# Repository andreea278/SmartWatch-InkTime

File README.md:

# SmartWatch InkTime 

Proiect de dezvoltare a unui ceas inteligent bazat pe microcontrolerul Nordic nRF52840, echipat cu un afișaj E-Ink și senzori pentru monitorizarea activității.

---

## Diagramă Bloc

---
Acest proiect reprezintă o platformă open-hardware de tip smartwatch, proiectată pentru flexibilitate maximă și eficiență energetică ridicată. Construit în jurul microcontrolerului nRF52840 , dispozitivul oferă control total la nivel de regiștri pentru proiecte embedded avansate.

- **[nRF52840](https://www.nordicsemi.com/Products/nRF52840)(Microcontroler):** System on Chip bazat pe ARM Cortex-M4F tactat la 64 MHz. Include suport nativ pentru Bluetooth 5 / BLE și radio 2.4 GHz. Dispune de 1 MB Flash și 256 KB RAM și oferă interfețe versatile: SPI, I2C, UART și GPIO pentru comunicarea cu celelalte module.
- **[E-Paper 1.54"](https://www.waveshare.com/wiki/1.54inch_e-Paper_Module):** Ecran cu consum redus de energie, rezoluție 200x200 pixeli, comunică cu MCU-ul prin interfața SPI.
- **[BQ25180](https://www.ti.com/product/BQ25180)(Încărcător LiPo):** IC pentru încărcarea bateriei Li-Ion/Li-Po, controlat prin I2C. Gestionează alimentarea de 5V de la portul USB și oferă funcții de *power path management*.
- **[MAX17048](https://www.analog.com/en/products/max17048.html)(Fuel Gauge):** Cip pentru monitorizarea precisă a nivelului bateriei (State-of-Charge).
- **[RT6160](https://www.richtek.com/Products/Switching%20Regulators/Buck-Boost%20Converter/RT6160)(Regulator Buck-Boost):** Reglează tensiunea bateriei pentru a furniza o ieșire stabilă de 3.3V necesară componentelor sistemului.
- **Baterie LiPo (250 mAh):** Sursa principală de energie a dispozitivului.
- **[USBLC6-2](https://www.st.com/en/protections-and-safety/usblc6-2.html) (Protecție USB):** Protecție ESD (Electrostatic Discharge) pentru portul USB-C, prevenind deteriorarea componentelor interne.
- **[BMA423](https://www.bosch-sensortec.com/products/motion-sensors/accelerometers/bma423/):** Senzor MEMS pe 3 axe, ultra-low-power, optimizat pentru wearables, oferind funcții integrate precum numărarea pașilor, recunoașterea activității și detectarea mișcării prin întreruperi.
- **[DRV2605L](https://www.ti.com/product/DRV2605L) (Driver Haptic):** Driver controlat prin I2C pentru motorul de vibrații.
- [FIT0774](https://www.dfrobot.com/product-2264.html): Shaker
-  **[TC2030-IDC](https://www.tag-connect.com/product/tc2030-idc/)**: Conector programare SWD.
- **Cristale de tact:**
  - **[32 MHz (X1)](https://www.digikey.ro/en/products/detail/abracon-llc/ABM8G-32.000MHZ-18-D2Y-T/2269926):** Asigură frecvența principală de operare pentru MCU.
  - **[32.768 kHz (X2)](https://www.digikey.ro/en/products/detail/epson/FC-135-32.7680KA-A3/4522301):** Folosit pentru ceasul de timp real (RTC) și menținerea acurateței temporale.

## Bill of Materials (BOM)

Aceasta este lista principală de componente pentru proiectul smartwatch-ului bazat pe nRF52840.

| Component | Descriere | Cantitate | Producător | Cod Piesă | Datasheet |
| :--- | :--- | :---: | :--- | :--- | :---: |
| **nRF52840** | BLE Microcontroller | 1 | Nordic Semiconductor | nRF52840 | [Link](https://files.seeedstudio.com/wiki/XIAO-BLE/Nano_BLE_MCU-nRF52840_PS_v1.1.pdf) |
| **BMA423** | Accelerometru 3-axe (IMU) | 1 | Bosch | BMA423 | [Link](https://watchy.sqfmi.com/assets/files/BST-BMA423-DS000-1509600-950150f51058597a6234dd3eaafbb1f0.pdf) |
| **BQ25180** | Încărcător baterie / PMIC | 1 | Texas Instruments | BQ25180 | [Link](https://www.ti.com/product/BQ25180) |
| **DRV2605L** | Driver haptic | 1 | Texas Instruments | DRV2605L | [Link](https://www.ti.com/product/BQ25180) |
| **MAX17048** | Fuel gauge | 1 | Analog Devices | MAX17048G+T10 | [Link](https://www.analog.com/en/products/max17048.html) |
| **RT6160** | Buck-boost converter | 1 | Richtek | RT6160AWSC | [Link](https://www.mouser.com/datasheet/2/1458/DS6160A_02-3104604.pdf) |
| **2450AT18B100E** | Antenă chip 2.4GHz | 1 | Johanson Technology | 2450AT18B100E | [Link](https://jlcpcb.com/api/file/downloadByFileSystemAccessId/8588940948130156544) |
| **TC2030-IDC** | Conector programare | 1 | Tag-Connect | TC2030-IDC | [Link](https://www.lcsc.com/datasheet/C5444772.pdf) |
| **USB-C Connector** | Interfață alimentare/date | 1 | Kinghelm | KH-TYPE-C-16P | [Link](https://jlcpcb.com/api/file/downloadByFileSystemAccessId/8588905154556923904) |
| **FPC Connector** | Conector display e-paper | 1 | Molex | 503480-2400 | [Link](https://www.molex.com/content/dam/molex/molexdotcom/products/automated/enus/salesdrawingpdf/503/503480/5034802400_sd.pdf?inline) |
| **Push Buttons** | Switch-uri tactile | 3 | Panasonic | EVP-AKE31A | [Link](https://wmsc.lcsc.com/wmsc/upload/file/pdf/v2/lcsc/2301111010_PANASONIC-EVPAKE31A_C569760.pdf) |
| **MOSFETs** | Comutare putere | 2 | Vishay / Diodes Inc. | SI1308EDL / DMG2305UX | [Link](https://www.lcsc.com/datasheet/C469327.pdf) |
| **Diodes** | Diode Schottky | 3 | ON Semiconductor | MBR0530 | [Link](https://www.lcsc.com/datasheet/C77336.pdf) |
| **ESD Protection** | Protecție USB | 1 | STMicroelectronics | USBLC6-2SC6 | [Link](https://www.lcsc.com/datasheet/C7519.pdf) |
| **Crystal** | 32MHz | 1 | NDK | NX2016SA-32MHZ-EXS00A-CS11336 | [Link](https://wmsc.lcsc.com/wmsc/upload/file/pdf/v2/lcsc/2312080231_NDK-NX2016SA-32MHZ-EXS00A-CS11336_C6134317.pdf) |
| **Crystals** | 32.768kHz | 1 | Seiko Epson | FC-135 32.7680KA-A3 | [Link](https://jlcpcb.com/partdetail/SeikoEpson-FC_135_32_7680KAA3/C2650472) |

---

##  Arhitectură și Specificații Hardware

### 1. Unitatea de Procesare (CPU)
* **Microcontroler:** **nRF52840 (Nordic Semiconductor)**
    * **Arhitectură:** ARM Cortex-M4F (cu FPU), tactat la 64 MHz.
    * **Capabilități:** Suport nativ Bluetooth 5.4 (BLE), radio 2.4 GHz.
    * **Memorie:** 1 MB Flash, 256 KB RAM.
    * **Rol:** Procesare centrală, gestionarea stivei Bluetooth și coordonarea perifericelor.

### 2. Sistemul de Management al Energiei (PMU)
Sistemul utilizează un lanț de alimentare eficient pentru a prelungi durata de viață a bateriei:

* **Încărcare (PMIC):** **BQ25180**
    * Gestionează alimentarea de 5V (USB-C) și oferă protecție integrată.
* **Reglare Tensiune:** **RT6160 (Buck-Boost)**
    * Converteste tensiunea bateriei (3.0V - 4.2V) la o linie stabilă de **3.3V** cu o eficiență de peste 90%.
* **Monitorizare:** **MAX17048 (Fuel Gauge)**
    * Algoritm *ModelGauge* pentru estimarea precisă a nivelului bateriei.
 
 ### 3. Matricea de Comunicare
Sistemul utilizează magistrale digitale pentru a minimiza numărul de pini ocupați:

| Protocol | Componente Conectate | Funcție |
| :--- | :--- | :--- |
| **SPI** | E-Paper Display | Transfer rapid de pixeli pentru refresh. |
| **I2C** | BMA423, BQ25180, DRV2605L, MAX17048 | Magistrală partajată pentru senzori și PMU. |
| **GPIO** | Butoane fizice, Interrupts (BMA423) | Input utilizator și wake-up trigger. |
| **SWD** | Conector TC2030-IDC | Interfață de programare și debugging. |

### 4. Periferice 
* **Afișaj:** E-Paper 1.54" (200x200).
    * *Avantaj:* Consum de energie zero pentru menținerea imaginii (bistabil).
* **Senzor:** **BMA423 (Accelerometru)**.
    * *Rol:* Detecția pașilor, recunoașterea activității și trezirea MCU-ului din `Deep Sleep`.
* **Feedback Haptic:** **DRV2605L** + Motor vibrații.
    * *Rol:* Driver haptic inteligent pentru feedback tactil avansat (click-uri, alerte), controlat via I2C.

---

## 4. Mapare Pini nRF52840

| Pin nRF52840 | Semnal | Componentă | Interfață |
| :--- | :--- | :--- | :--- |
| **P0.00** | XL1 | Cristal X2 (32.768kHz) | XTAL |
| **P0.01** | XL2 | Cristal X2 (32.768kHz) | XTAL |
| **P0.02** | SCK | E-Paper (J1 FPC) | SPI SCK |
| **P0.03** | MOSI | E-Paper (J1 FPC) | SPI MOSI |
| **P0.05** | EPD_CS | E-Paper (J1 FPC) | SPI CS |
| **P0.06** | SDA | BMA423, BQ25180, MAX17048, DRV2605 | I2C SDA |
| **P0.07** | SCL | BMA423, BQ25180, MAX17048, DRV2605 | I2C SCL |
| **P0.08** | IMU_INT1 | BMA423 | GPIO Input |
| **P1.08** | IMU_INT2 | BMA423 | GPIO Input |
| **P0.10** | ALERT | MAX17048 | GPIO Input |
| **P0.11** | PMIC_INT | BQ25180 | GPIO Input |
| **P0.12** | HAPTIC_EN | DRV2605 | GPIO Output |
| **P0.13** | SW_UP | Buton Up | GPIO Input |
| **P0.14** | SW_ENT | Buton Enter | GPIO Input |
| **P0.15** | EPD_DC | E-Paper (J1 FPC) | GPIO |
| **P0.16** | EPD_RST | E-Paper (J1 FPC) | GPIO |
| **P0.17** | EPD_BUSY | E-Paper (J1 FPC) | GPIO Input |
| **P0.18** | RESET | TC2030-IDC | SWD / Reset |
| **P1.02** | SW_DN | Buton Down | GPIO Input |
| **SWDCLK** | SWDCLK | TC2030-IDC | SWD |
| **SWDIO** | SWDIO | TC2030-IDC | SWD |
| **ANT** | RF | Antenă 2450AT18B100E | RF |

---
## 5. Specificații Design PCB

### Reguli de Proiectare 
* **Strat 1 (Top):** Componente și rutare semnal.
* **Strat 2 (Internal):** Plan Putere (VCC/3V3).
* **Strat 3 (Internal):** Plan Masă (GND).
* **Strat 4 (Bottom):** Rutare semnal și componente.

### Constrângeri DRC
* **Trasee Putere:** 0.3 mm (îngustate sub BGA).
* **Trasee Date:** 0.15 mm (min).
* **Unghiuri:** Doar 45° sau rotunjite.
* **Antenă:** Zonă "Keep-out" (fără cupru) pe toate straturile sub antenă.
* **Decuplare:** Condensatoarele de 100nF plasate direct pe pinii de alimentare.

### Erori DRC Acceptate
* **Copper Clearance (Aprobat):** În zona fan-out-ului pentru nRF52840, clearance-ul a fost redus manual sub 0.15mm pentru a permite rutarea corectă a pinilor AQFN cu pitch mic.

---

### Design PCB
| **Top Layer** | **Bottom Layer** | **Silkscreen** |
| :---: | :---: | :---: |
|  |  |  |
| **Inner Layer 2 (GND)** | **Inner Layer 3 (Power - C63)** |
|  |  |

### Design Schematic
---

| Pagina 1 - MCU & Power | Pagina 2 - Display & Senzori |
|:---:|:---:|
|  width="300" |  width="300" |

---

### 3D PCB & Carcasa
| **Top View** | 
| :---: | 
|  | 
**Side View** |
|  |
|  **SmartWatch Components** |
|  |

---

## 6. Structură 
* `Hardware/` - Fișierele sursă `.sch` și `.brd` .
* `Manufacturing/` - Fișiere Gerber, BOM și Pick & Place.
* `Mechanical/` - Modelul 3D al dispozitivului în format `.f3d` și `.step` (exploded view).
* `Images/` - Randări și screenshot-uri ale proiectului.

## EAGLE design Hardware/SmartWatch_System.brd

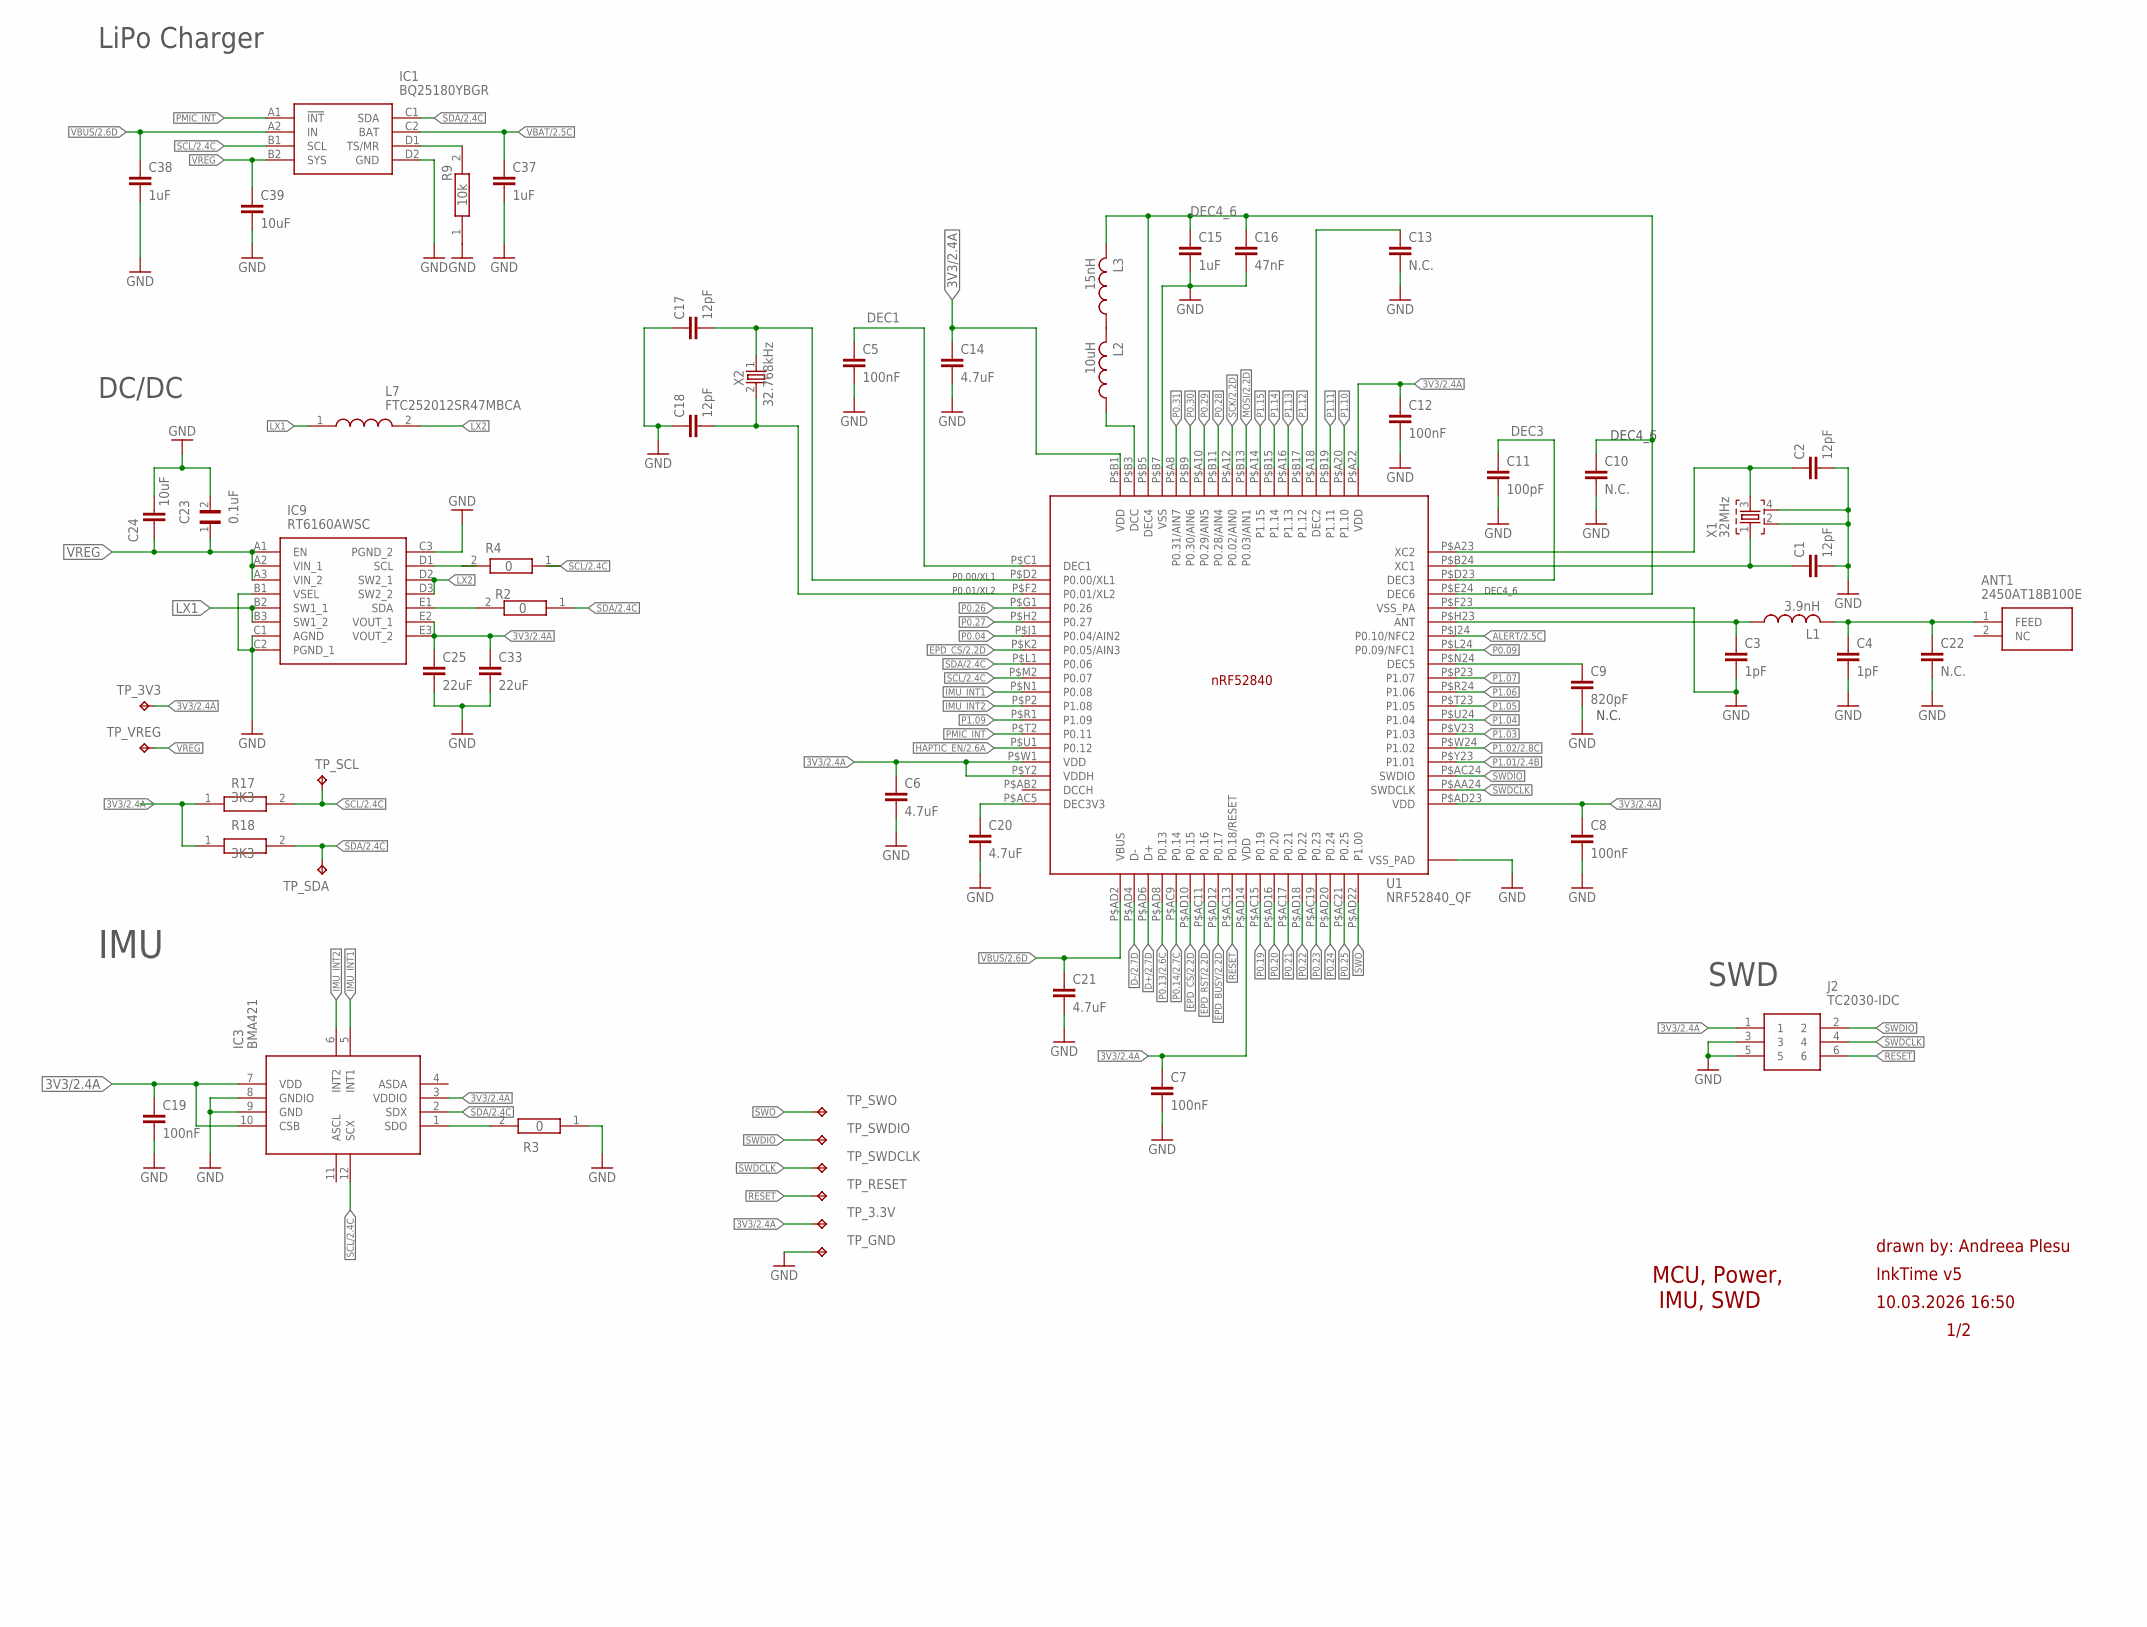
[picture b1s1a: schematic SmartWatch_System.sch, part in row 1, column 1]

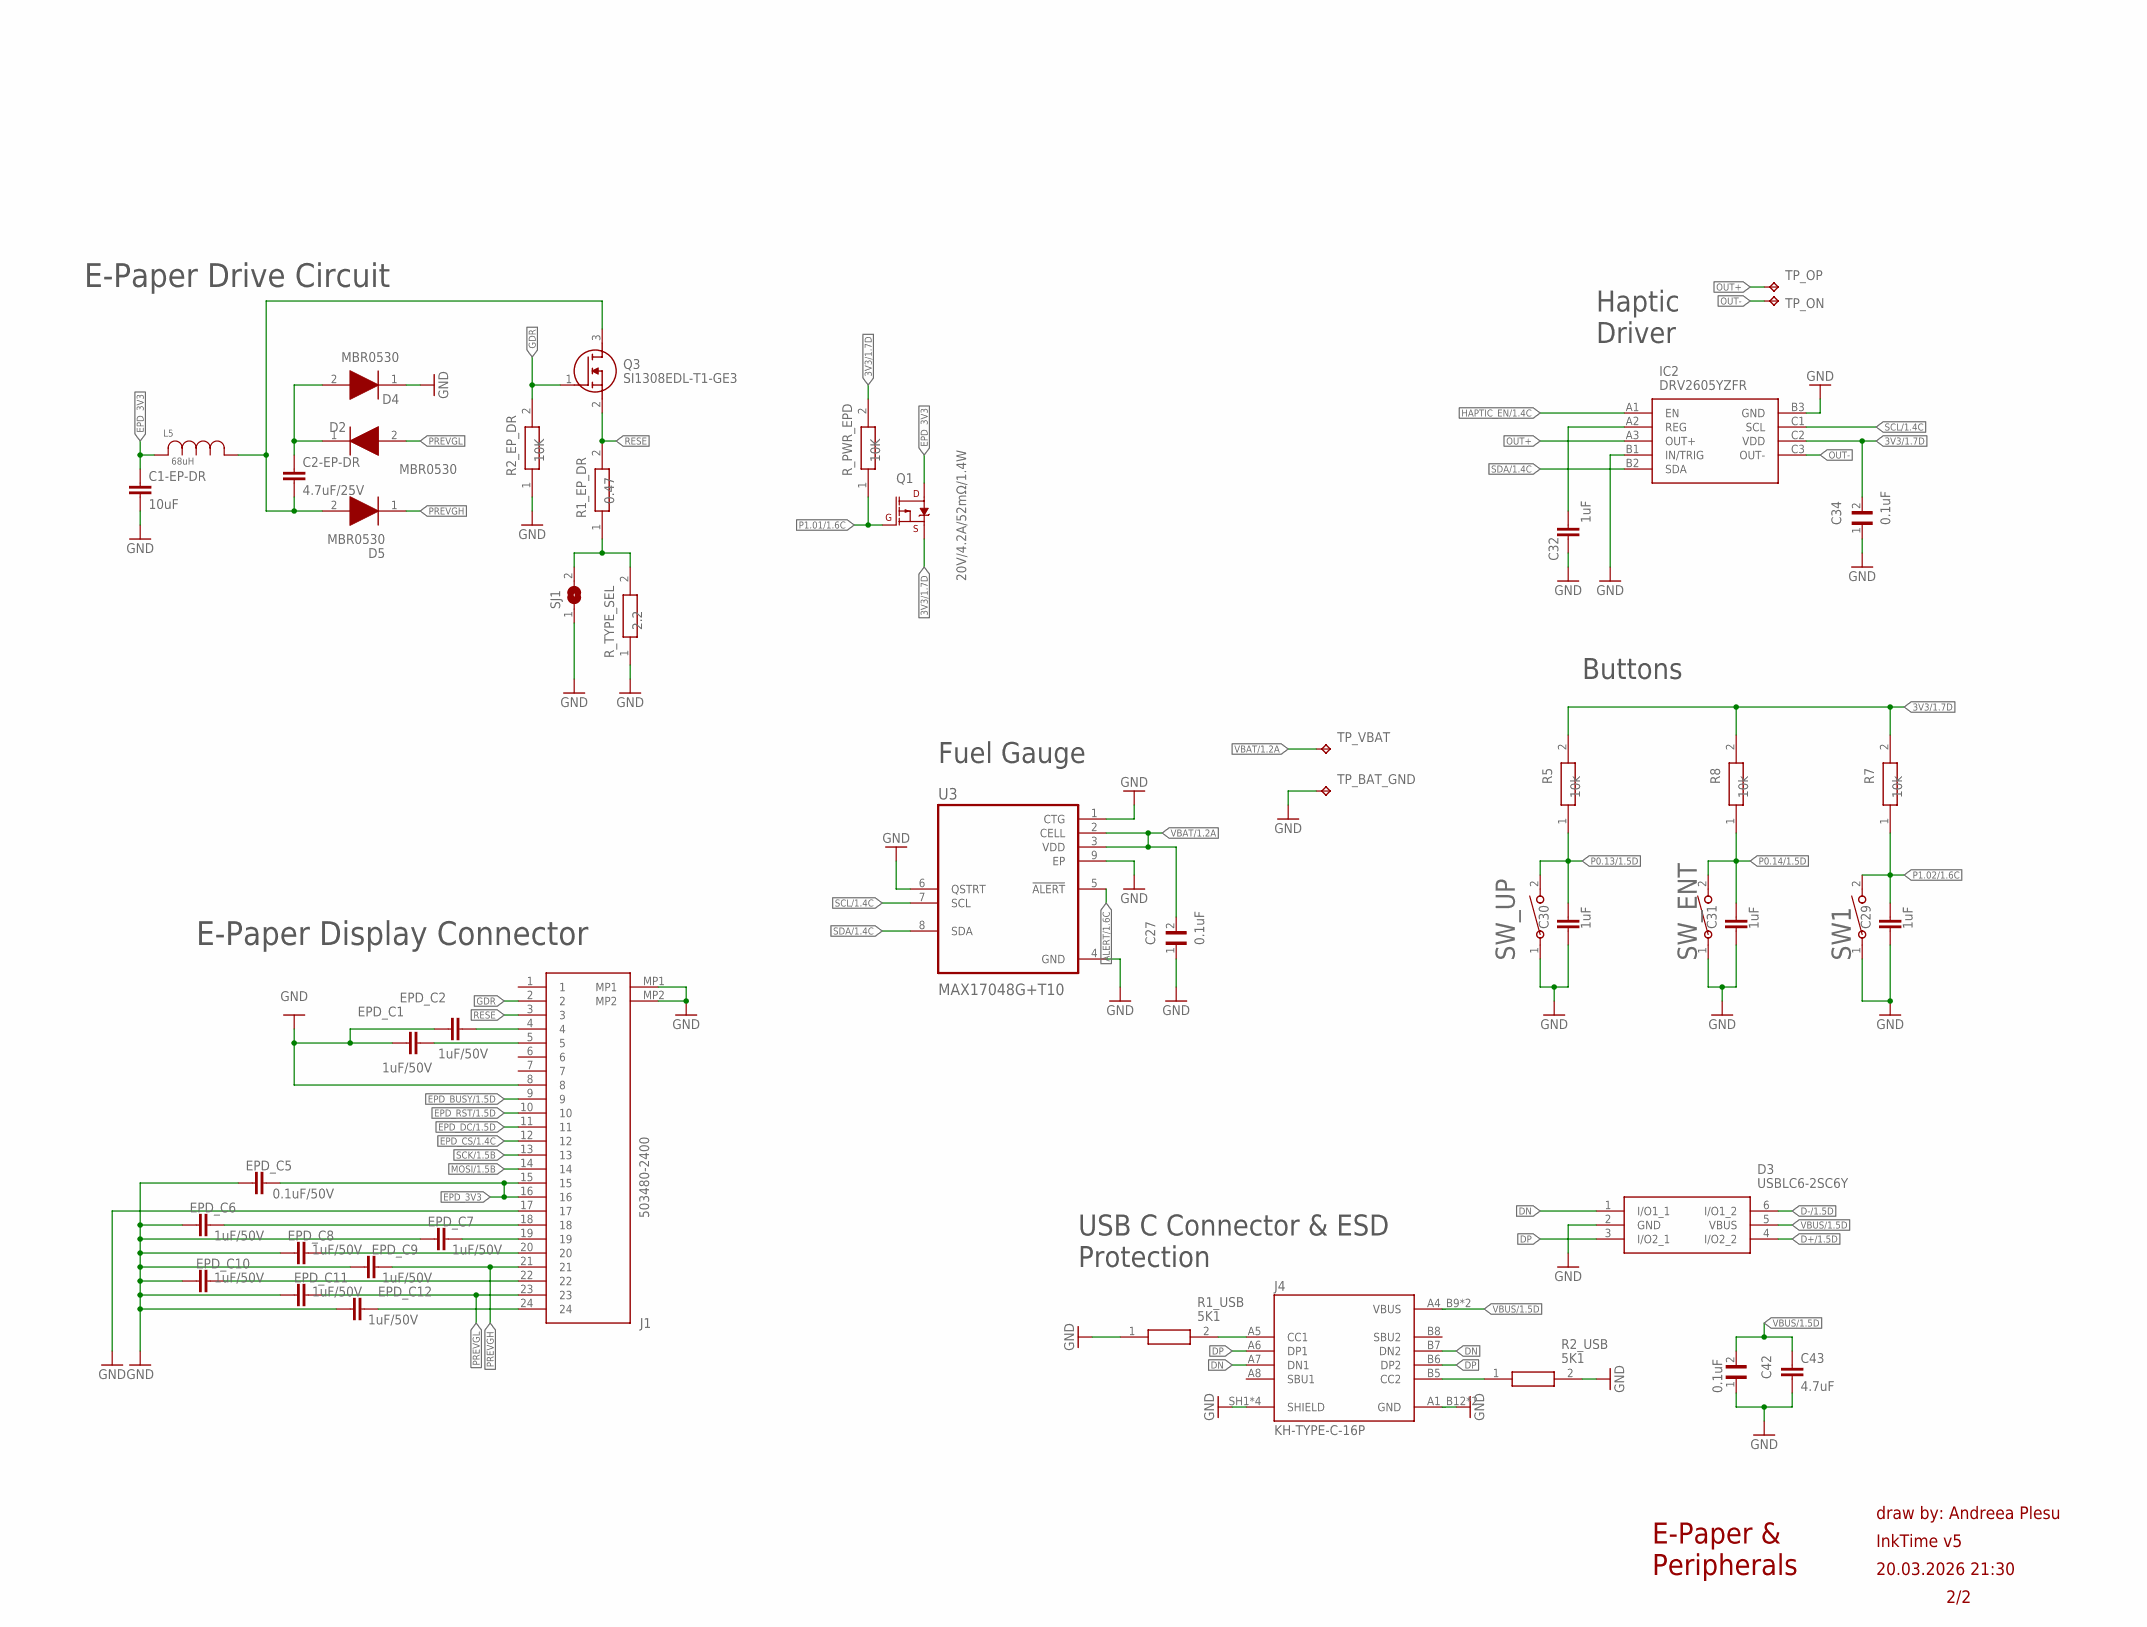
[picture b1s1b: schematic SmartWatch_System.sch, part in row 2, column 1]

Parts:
ANT1: 2450AT18B100E; 2450AT18B100E_ANTC3216X140N
C1, C2, C17, C18: 12pF; NORDIC_NRF_3_RESC0201_L
C1-EP-DR: 10uF; NORDIC_NRF_3_RESC0402_L
C2-EP-DR: 4.7uF/25V; NORDIC_NRF_3_RESC0402_L
C3, C4: 1pF; NORDIC_NRF_3_RESC0201_L
C5, C7, C8, C12, C19: 100nF; NORDIC_NRF_3_RESC0201_L
C6, C20, C21: 4.7uF; NORDIC_NRF_3_RESC0402_L
C9: 820pF; NORDIC_NRF_3_RESC0201_L
C10, C13, C22: N.C.; NORDIC_NRF_3_RESC0201_L
C11: 100pF; NORDIC_NRF_3_RESC0201_L
C14, C43: 4.7uF; PERFECT_0402_0402
C15, C29, C30, C31, C37, C38: 1uF; PERFECT_0402_0402
C16: 47nF; NORDIC_NRF_3_RESC0201_L
C23, C27: 0.1uF; GRM011R60J152KE01L_2_CAPC0201X13N
C24, C39: 10uF; PERFECT_0402_0402
C25, C33: 22uF; NORDIC_NRF_3_RESC0402_L
C32: 1uF; NORDIC_NRF_3_RESC0402_L
C34, C42: 0.1uF; NORDIC_NRF_3_RESC0201_L
D2, D4, D5: MBR0530; ESP32_C6_LIBRARY_5_SOD3716X135N
D3: USBLC6-2SC6Y; ESP32_C6_LIBRARY_3_SOT95P280X145-6N
EPD_C1, EPD_C2, EPD_C6, EPD_C7, EPD_C8, EPD_C9, EPD_C10, EPD_C11, EPD_C12: 1uF/50V; NORDIC_NRF_3_RESC0402_L
EPD_C5: 0.1uF/50V; NORDIC_NRF_3_RESC0201_L
IC1: BQ25180YBGR; BQ25180YBGR_BGA8C40P2X4_100X155X50
IC2: DRV2605YZFR; DRV2605YZFR_BGA9C50P3X3_144X144X62
IC3: BMA421; BMA423_BMA423
IC9: RT6160AWSC; RT6160AWSC_BGA15C40P3X5_140X230X60
J1: 503480-2400; 503480-2400_5034802400
J2: TC2030-IDC; TC2030-IDC_TC2030IDC
J4: KH-TYPE-C-16P; KH-TYPE-C-16P_KINGHELM_KH-TYPE-C-16P
L1: 3.9nH; NORDIC_NRF_2_RESC0402_L
L2: 10uH; NORDIC_NRF_2_RESC0402_L
L3: 15nH; NORDIC_NRF_2_RESC0402_L
L5: 68uH; ESP32_C6_LIBRARY_2_IND_4828-WE-TPC_WRE
L7: FTC252012SR47MBCA; MLP2016SR47MT0S1_INDC2016X100N
Q1: 20V/4.2A/52mΩ/1.4W; ESP32_C6_LIBRARY_4_ESP32_C6_LIBRARY_4_ESP32_C6_LIBRARY_4_ES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
Q3: SI1308EDL-T1-GE3; ESP32_C6_LIBRARY_6_SOT65P210X110-3N
R1_EP_DR: 0.47; CPF0201D7K68C1_0201
R1_USB, R2_USB: 5K1; CPF0201D7K68C1_0201
R2, R4: 0; ERA-1AEB3401C_0201
R2_EP_DR: 10K; CPF0201D7K68C1_0201
R3: 0; CPF0201D7K68C1_0201
R5, R7, R8: 10k; CPF0201D7K68C1_0201
R9: 10k; ERA-1AEB3401C_0201
R17, R18: 3K3; ERA-1AEB3401C_0201
R_PWR_EPD: 10K; CPF0201D7K68C1_0201
R_TYPE_SEL: 2.2; CPF0201D7K68C1_0201
SJ1: ESP32_C6_LIBRARY_7_JUMPER_SJ
SW1: 2025-10-22_07-23-44_LIBRARY_EVP-AKE31ASW_EVP-AKE3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; 2025-10-22_07-23-44_LIBRARY_SW_EVP-AKE31A_PAN
SW_ENT: 2025-10-22_07-23-44_LIBRARY_EVP-AKE31ASW_EVP-AKE3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; 2025-10-22_07-23-44_LIBRARY_SW_EVP-AKE31A_PAN
SW_UP: 2025-10-22_07-23-44_LIBRARY_EVP-AKE31ASW_EVP-AKE3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; 2025-10-22_07-23-44_LIBRARY_SW_EVP-AKE31A_PAN
TP_3.3V, TP_3V3: HECTOR_WATCH_1_TPTP20R; HECTOR_WATCH_1_TP20R
TP_BAT_GND: HECTOR_WATCH_1_TPTP20R; HECTOR_WATCH_1_TP20R
TP_GND: HECTOR_WATCH_1_TPTP20R; HECTOR_WATCH_1_TP20R
TP_ON: HECTOR_WATCH_1_TPTP20R; HECTOR_WATCH_1_TP20R
TP_OP: HECTOR_WATCH_1_TPTP20R; HECTOR_WATCH_1_TP20R
TP_RESET: HECTOR_WATCH_1_TPTP20R; HECTOR_WATCH_1_TP20R
TP_SCL: HECTOR_WATCH_1_TPTP20R; HECTOR_WATCH_1_TP20R
TP_SDA: HECTOR_WATCH_1_TPTP20R; HECTOR_WATCH_1_TP20R
TP_SWDCLK: HECTOR_WATCH_1_TPTP20R; HECTOR_WATCH_1_TP20R
TP_SWDIO: HECTOR_WATCH_1_TPTP20R; HECTOR_WATCH_1_TP20R
TP_SWO: HECTOR_WATCH_1_TPTP20R; HECTOR_WATCH_1_TP20R
TP_VBAT: HECTOR_WATCH_1_TPTP20R; HECTOR_WATCH_1_TP20R
TP_VREG: HECTOR_WATCH_1_TPTP20R; HECTOR_WATCH_1_TP20R
U1: NRF52840_QF; NORDIC_NRF_4_AQFN50P700X700X85_HS-74N
U3: MAX17048G+T10; ESP32_C6_LIBRARY_SON50P200X200X80-9N
X1: 32MHz; NORDIC_NRF_BT-XTAL_2016_N
X2: 32.768kHz; NORDIC_NRF_1_XTAL_3215_N

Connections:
3V3/1.7D: C34.2, IC2.C2 (VDD), Q1.2 (S), R5.2, R7.2, R8.2, R_PWR_EPD.2
3V3/2.4A: C6.1, C7.1, C8.1, C12.1, C14.1, C19.1, C25.1, C33.1, IC3.3 (VDDIO), IC3.7 (VDD), IC3.10 (CSB), IC9.E2 (VOUT_1), IC9.E3 (VOUT_2), J2.1, R17.1, R18.1, TP_3.3V.TP, TP_3V3.TP, U1.P$A22 (VDD), U1.P$AD14 (VDD), U1.P$AD23 (VDD), U1.P$B1 (VDD), U1.P$W1 (VDD), U1.P$Y2 (VDDH)
ALERT/1.6C: U3.5 (!ALERT)
ALERT/2.5C: U1.P$J24 (P0.10/NFC2)
D+/1.5D: D3.4 (I/O2_2)
D+/2.7D: U1.P$AD6 (D+)
D-/1.5D: D3.6 (I/O1_2)
D-/2.7D: U1.P$AD4 (D-)
DEC1: C5.1, U1.P$C1 (DEC1)
DEC3: C11.1, U1.P$D23 (DEC3)
DEC4_6: C10.1, C15.1, C16.1, L3.2, U1.P$B5 (DEC4), U1.P$E24 (DEC6)
DN: D3.1 (I/O1_1), J4.A7 (DN1), J4.B7 (DN2)
DP: D3.3 (I/O2_1), J4.A6 (DP1), J4.B6 (DP2)
EPD_3V3: C1-EP-DR.1, EPD_C5.2, J1.15, J1.16, L5.2, Q1.3 (D)
EPD_BUSY/1.5D: J1.9
EPD_BUSY/2.2D: U1.P$AD12 (P0.17)
EPD_CS/1.4C: J1.12
EPD_CS/2.2D: U1.P$AD10 (P0.15), U1.P$K2 (P0.05/AIN3)
EPD_DC/1.5D: J1.11
EPD_RST/1.5D: J1.10
EPD_RST/2.2D: U1.P$AC11 (P0.16)
GDR: J1.2, Q3.1 (G), R2_EP_DR.2
GND: C1.2, C1-EP-DR.2, C2.2, C3.2, C4.2, C5.2, C6.2, C7.2, C8.2, C9.2, C10.2, C11.2, C12.2, C13.2, C14.2, C15.2, C16.2, C17.1, C18.1, C19.2, C20.2, C21.2, C22.2, C23.2, C24.2, C25.2, C27.1, C29.2, C30.2, C31.2, C32.2, C33.2, C34.1, C37.2, C38.2, C39.2, C42.1, C43.2, D3.2 (GND), D4.1 (K), EPD_C1.1, EPD_C2.1, EPD_C5.1, EPD_C6.1, EPD_C7.1, EPD_C8.1, EPD_C9.1, EPD_C10.1, EPD_C11.1, EPD_C12.1, IC1.D2 (GND), IC2.B1 (IN/TRIG), IC2.B3 (GND), IC3.8 (GNDIO), IC3.9 (GND), IC9.B1 (VSEL), IC9.C1 (AGND), IC9.C2 (PGND_1), IC9.C3 (PGND_2), J1.8, J1.17, J1.MP1, J1.MP2, J2.3, J2.5, J4.A1_B12 (GND), J4.A12_B1 (GND), J4.SH1 (SHIELD), J4.SH2 (SHIELD), J4.SH3 (SHIELD), J4.SH4 (SHIELD), R1_USB.1, R2_EP_DR.1, R2_USB.2, R3.1, R9.1, R_TYPE_SEL.1, SJ1.1, SW1.1, SW_ENT.1, SW_UP.1, TP_BAT_GND.TP, TP_GND.TP, U1.P$74 (VSS_PAD), U1.P$75 (VSS_PAD), U1.P$76 (VSS_PAD), U1.P$77 (VSS_PAD), U1.P$78 (VSS_PAD), U1.P$79 (VSS_PAD), U1.P$80 (VSS_PAD), U1.P$81 (VSS_PAD), U1.P$82 (VSS_PAD), U1.P$83 (VSS_PAD), U1.P$84 (VSS_PAD), U1.P$85 (VSS_PAD), U1.P$86 (VSS_PAD), U1.P$87 (VSS_PAD), U1.P$88 (VSS_PAD), U1.P$89 (VSS_PAD), U1.P$90 (VSS_PAD), U1.P$B7 (VSS), U1.P$F23 (VSS_PA), U3.1 (CTG), U3.4 (GND), U3.6 (QSTRT), U3.9 (EP), X1.2, X1.4
HAPTIC_EN/1.4C: IC2.A1 (EN)
HAPTIC_EN/2.6A: U1.P$U1 (P0.12)
IMU_INT1: IC3.5 (INT1), U1.P$N1 (P0.08)
IMU_INT2: IC3.6 (INT2), U1.P$P2 (P1.08)
LX1: IC9.B2 (SW1_1), IC9.B3 (SW1_2), L7.1
LX2: IC9.D2 (SW2_1), IC9.D3 (SW2_2), L7.2
MOSI/1.5B: J1.14
MOSI/2.2D: U1.P$B13 (P0.03/AIN1)
unnamed: IC1.D1 (TS/MR), R9.2
unnamed: IC9.D1 (SCL), R4.2
unnamed: IC9.E1 (SDA), R2.2
unnamed: L2.2, L3.1
unnamed: L2.1, U1.P$B3 (DCC)
unnamed: IC3.1 (SDO), R3.2
unnamed: C13.1, U1.P$A18 (DEC2)
unnamed: C17.2, U1.P$D2 (P0.00/XL1), X2.1
unnamed: C18.2, U1.P$F2 (P0.01/XL2), X2.2
unnamed: C20.1, U1.P$AC5 (DEC3V3)
unnamed: C1.1, U1.P$B24 (XC1), X1.1
unnamed: C2.1, U1.P$A23 (XC2), X1.3
unnamed: C9.1, U1.P$N24 (DEC5)
unnamed: C3.1, L1.1, U1.P$H23 (ANT)
unnamed: ANT1.1 (FEED), C4.1, C22.1, L1.2
unnamed: C2-EP-DR.1, D2.1 (K), D4.2 (A)
unnamed: C2-EP-DR.2, D5.2 (A), L5.1, Q3.3 (D)
unnamed: R1_EP_DR.1, R_TYPE_SEL.2, SJ1.2
unnamed: EPD_C2.2, J1.4
unnamed: EPD_C1.2, J1.5
unnamed: EPD_C6.2, J1.18
unnamed: EPD_C7.2, J1.19
unnamed: EPD_C8.2, J1.20
unnamed: C32.1, IC2.A2 (REG)
unnamed: EPD_C10.2, J1.22
unnamed: J4.B5 (CC2), R2_USB.1
unnamed: EPD_C12.2, J1.24
unnamed: J4.A5 (CC1), R1_USB.2
OUT+: IC2.A3 (OUT+), TP_OP.TP
OUT-: IC2.C3 (OUT-), TP_ON.TP
P0.04: U1.P$J1 (P0.04/AIN2)
P0.09: U1.P$L24 (P0.09/NFC1)
P0.13/1.5D: C30.1, R5.1, SW_UP.2
P0.13/2.6C: U1.P$AD8 (P0.13)
P0.14/1.5D: C31.1, R8.1, SW_ENT.2
P0.14/2.7C: U1.P$AC9 (P0.14)
P0.19: U1.P$AC15 (P0.19)
P0.20: U1.P$AD16 (P0.20)
P0.21: U1.P$AC17 (P0.21)
P0.22: U1.P$AD18 (P0.22)
P0.23: U1.P$AC19 (P0.23)
P0.24: U1.P$AD20 (P0.24)
P0.25: U1.P$AC21 (P0.25)
P0.26: U1.P$G1 (P0.26)
P0.27: U1.P$H2 (P0.27)
P0.28: U1.P$B11 (P0.28/AIN4)
P0.29: U1.P$A10 (P0.29/AIN5)
P0.30: U1.P$B9 (P0.30/AIN6)
P0.31: U1.P$A8 (P0.31/AIN7)
P1.01/1.6C: Q1.1 (G), R_PWR_EPD.1
P1.01/2.4B: U1.P$Y23 (P1.01)
P1.02/1.6C: C29.1, R7.1, SW1.2
P1.02/2.8C: U1.P$W24 (P1.02)
P1.03: U1.P$V23 (P1.03)
P1.04: U1.P$U24 (P1.04)
P1.05: U1.P$T23 (P1.05)
P1.06: U1.P$R24 (P1.06)
P1.07: U1.P$P23 (P1.07)
P1.09: U1.P$R1 (P1.09)
P1.10: U1.P$A20 (P1.10)
P1.11: U1.P$B19 (P1.11)
P1.12: U1.P$B17 (P1.12)
P1.13: U1.P$A16 (P1.13)
P1.14: U1.P$B15 (P1.14)
P1.15: U1.P$A14 (P1.15)
PMIC_INT: IC1.A1 (!INT), U1.P$T2 (P0.11)
PREVGH: D5.1 (K), EPD_C9.2, J1.21
PREVGL: D2.2 (A), EPD_C11.2, J1.23
RESE: J1.3, Q3.2 (S), R1_EP_DR.2
RESET: J2.6, TP_RESET.TP, U1.P$AC13 (P0.18/RESET)
SCK/1.5B: J1.13
SCK/2.2D: U1.P$A12 (P0.02/AIN0)
SCL/1.4C: IC2.C1 (SCL), U3.7 (SCL)
SCL/2.4C: IC1.B1 (SCL), IC3.12 (SCX), R4.1, R17.2, TP_SCL.TP, U1.P$M2 (P0.07)
SDA/1.4C: IC2.B2 (SDA), U3.8 (SDA)
SDA/2.4C: IC1.C1 (SDA), IC3.2 (SDX), R2.1, R18.2, TP_SDA.TP, U1.P$L1 (P0.06)
SWDCLK: J2.4, TP_SWDCLK.TP, U1.P$AA24 (SWDCLK)
SWDIO: J2.2, TP_SWDIO.TP, U1.P$AC24 (SWDIO)
SWO: TP_SWO.TP, U1.P$AD22 (P1.00)
VBAT/1.2A: C27.2, TP_VBAT.TP, U3.2 (CELL), U3.3 (VDD)
VBAT/2.5C: C37.1, IC1.C2 (BAT)
VBUS/1.5D: C42.2, C43.1, D3.5 (VBUS), J4.A4_B9 (VBUS), J4.A9_B4 (VBUS)
VBUS/2.6D: C21.1, C38.1, IC1.A2 (IN), U1.P$AD2 (VBUS)
VREG: C23.1, C24.1, C39.1, IC1.B2 (SYS), IC9.A1 (EN), IC9.A2 (VIN_1), IC9.A3 (VIN_2), TP_VREG.TP

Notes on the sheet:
LiPo Charger
DC/DC
IMU
P0.00/XL1
P0.01/XL2
DEC4_6
N.C.
SWD
MCU, Power, IMU, SWD
drawn by: Andreea Plesu
InkTime v5
10.03.2026 16:50
1/2
E-Paper Drive Circuit
E-Paper Display Connector
Fuel Gauge
Haptic Driver
Buttons
USB C Connector & ESD Protection
E-Paper & Peripherals
draw by: Andreea Plesu
20.03.2026 21:30
2/2

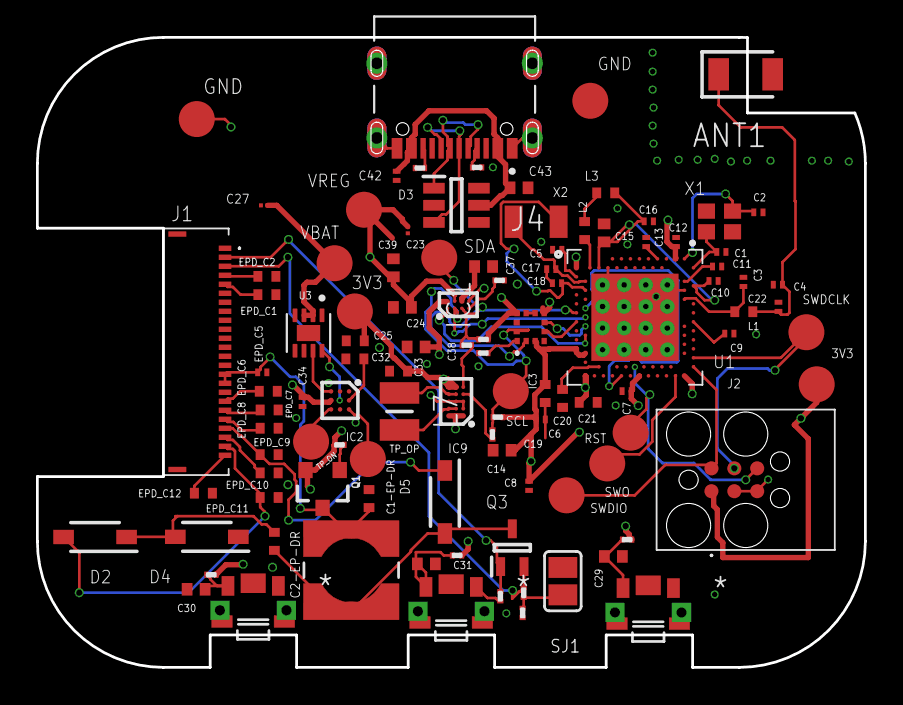
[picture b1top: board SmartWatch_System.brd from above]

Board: 4 copper layers, 46.0 x 35.0 mm, 105 parts (0 on the bottom side), 66 nets.

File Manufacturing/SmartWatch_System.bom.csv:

Reference Designators;Quantity;Description;Package;Value;Manufacturer;Manufacturer Part Number;Vendor;Vendor Part Number;Top/Bottom;
;1;PCB Board;Board;;;;;;;
ANT1;1;Antennas 2.45GHz ANTENNA;2450AT18B100E_ANTC3216X140N;2450AT18B100E;;;;;Top;
C1-EP-DR;1;Generic chip capacitor;NORDIC_NRF_3_RESC0402_L;10uF;;;;;Top;
C1, C2, C17, C18;4;Generic chip capacitor;NORDIC_NRF_3_RESC0201_L;12pF;;;;;Top;
C2-EP-DR;1;Generic chip capacitor;NORDIC_NRF_3_RESC0402_L;4.7uF/25V;;;;;Top;
C3, C4;2;Generic chip capacitor;NORDIC_NRF_3_RESC0201_L;1pF;;;;;Top;
C5;1;CAPACITOR, European symbol;HPC0201;100nF;;;;;Top;
C6, C20, C21;3;Generic chip capacitor;NORDIC_NRF_3_RESC0402_L;4.7uF;;;;;Top;
C7, C8, C12, C19;4;Generic chip capacitor;NORDIC_NRF_3_RESC0201_L;100nF;;;;;Top;
C9;1;Generic chip capacitor;NORDIC_NRF_3_RESC0201_L;820pF;;;;;Top;
C10, C13, C22;3;Generic chip capacitor;NORDIC_NRF_3_RESC0201_L;N.C.;;;;;Top;
C11;1;Generic chip capacitor;NORDIC_NRF_3_RESC0201_L;100pF;;;;;Top;
C14;1;CAPACITOR, European symbol;ESP32_WROVER_EAGLE-LTSPICE_C0402;4.7uF;;;;;Top;
C15, C29, C30, C31;4;0402 (1005 Metric);PERFECT_0402_0402;1uF;;;;;Top;
C16;1;Generic chip capacitor;NORDIC_NRF_3_RESC0201_L;47nF;;;;;Top;
C23;1;CAPACITOR, European symbol;HPC0201;0.1uF;;;;;Top;
C24, C39;2;CAPACITOR, European symbol;ESP32_WROVER_EAGLE-LTSPICE_C0402;10uF;;;;;Top;
C25, C33;2;Generic chip capacitor;NORDIC_NRF_3_RESC0402_L;22uF;;;;;Top;
C27;1;Check availability;CAPC0201X13N;0.1uF;;;;;Top;
C32;1;Generic chip capacitor;NORDIC_NRF_3_RESC0402_L;1uF;;;;;Top;
C34, C42;2;Check availability;GRM011R60J152KE01L_1_0201;0.1uF;;;;;Top;
C37, C38;2;CAPACITOR, European symbol;ESP32_WROVER_EAGLE-LTSPICE_C0402;1uF;;;;;Top;
C43;1;0402 (1005 Metric);PERFECT_0402_0402;4.7uF;;;;;Top;
D2, D4, D5;3;ON SEMICONDUCTOR - MBR0530 - DIODE, SCHOTTKY, 0.5A, 30V, SOD-123;SOD3716X135N;MBR0530;;;;;Top;
D3;1;Low Cap. ESD Protection Auto SOT-23-6 STMicroelectronics USBLC6-2SC6Y, Dual Uni-Directional TVS Diode Array, 6-Pin SOT-23;SOT95P280X145-6N;USBLC6-2SC6Y;;;;;Top;
EPD_C1, EPD_C2, EPD_C6, EPD_C7, EPD_C8, EPD_C9, EPD_C10, EPD_C11, EPD_C12;9;Generic chip capacitor;NORDIC_NRF_3_RESC0402_L;1uF/50V;;;;;Top;
EPD_C5;1;Generic chip capacitor;NORDIC_NRF_3_RESC0201_L;0.1uF/50V;;;;;Top;
IC1;1;Charger IC Lithium Ion/Polymer, Lithium Iron Phosphate 8-DSBGA (1.6x1.1);BQ25180YBGR_BGA8C40P2X4_100X155X50;BQ25180YBGR;;;;;Top;
IC2;1;Haptic Driver for ERM/LRA with Built-In Library and Smart Loop Architecture;DRV2605YZFR_BGA9C50P3X3_144X144X62;DRV2605YZFR;;;;;Top;
IC3;1;Accelerometers Triaxial low-g 12bit Acceleration Sensor;BMA423_BMA423;BMA421;;;;;Top;
IC9;1;Buck-Boost Regulator Positive Output Step-Up/Step-Down I2C DC-DC Controller IC 15-WL-CSP (BSC) (1.4x2.3);RT6160AWSC_BGA15C40P3X5_140X230X60;RT6160AWSC;;;;;Top;
J1;1;FFC & FPC Connectors 0.5mm FPC RA SMT Dual Contact 24Ckt;503480-2400_5034802400;503480-2400;;;;;Top;
J2;1;CABLE ADAPTER 6 POS;TC2030-IDC_TC2030IDC;TC2030-IDC;;;;;Top;
J4;1;Check availability;KINGHELM_KH-TYPE-C-16P;KH-TYPE-C-16P;;;;;Top;
L1;1;Generic chip inductor;NORDIC_NRF_2_RESC0402_L;3.9nH;;;;;Top;
L2;1;Generic chip inductor;NORDIC_NRF_2_RESC0402_L;10uH;;;;;Top;
L3;1;Generic chip inductor;NORDIC_NRF_2_RESC0402_L;15nH;;;;;Top;
L5;1;;ESP32_C6_LIBRARY_2_IND_4828-WE-TPC_WRE;68uH;;;;;Top;
L7;1;SMD / SMT Inductors (Coils), L=0.47?H, L x W x T :;MLP2016SR47MT0S1_INDC2016X100N;FTC252012SR47MBCA;;;;;Top;
Q1;1;P-channel MOSFETs;ESP32_WROVER_SPARKFUN-DISCRETESEMI_SOT23-3;20V/4.2A/52mΩ/1.4W;;;;;Top;
Q3;1;MOSFET N-Ch 30V 1.5A TrenchFET SC70 Vishay Si1308EDL-T1-GE3 N-channel MOSFET Transistor, 1.5 A, 30 V, 3-Pin SC-70;SOT65P210X110-3N;SI1308EDL-T1-GE3;;;;;Top;
R_PWR_EPD, R2_EP_DR;2;7.68k 0201 Thin Film Surface Mount Fixed Resistor +/-0.5% 0.031W CPF0201D7K68C1;CPF0201D7K68C1_0201;10K;;;;;Top;
R_TYPE_SEL;1;7.68k 0201 Thin Film Surface Mount Fixed Resistor +/-0.5% 0.031W CPF0201D7K68C1;CPF0201D7K68C1_0201;2.2;;;;;Top;
R1_EP_DR;1;7.68k 0201 Thin Film Surface Mount Fixed Resistor +/-0.5% 0.031W CPF0201D7K68C1;CPF0201D7K68C1_0201;0.47;;;;;Top;
R1_USB, R2_USB;2;7.68k 0201 Thin Film Surface Mount Fixed Resistor +/-0.5% 0.031W CPF0201D7K68C1;CPF0201D7K68C1_0201;5K1;;;;;Top;
R2, R4;2;RESISTOR, European symbol;R0201;0;;;;;Top;
R3;1;7.68k 0201 Thin Film Surface Mount Fixed Resistor +/-0.5% 0.031W CPF0201D7K68C1;CPF0201D7K68C1_0201;0;;;;;Top;
R5, R7, R8;3;7.68k 0201 Thin Film Surface Mount Fixed Resistor +/-0.5% 0.031W CPF0201D7K68C1;CPF0201D7K68C1_0201;10k;;;;;Top;
R9;1;7.68k 0201 Thin Film Surface Mount Fixed Resistor +/-0.5% 0.031W CPF0201D7K68C1;R0201;10K;;;;;Top;
R17, R18;2;7.68k 0201 Thin Film Surface Mount Fixed Resistor +/-0.5% 0.031W CPF0201D7K68C1;R0201;3K3;;;;;Top;
SJ1;1;SMD solder JUMPER;JUMPER_SJ;;;;;;Top;
SW_ENT, SW_UP, SW1;3;;SW_EVP-AKE31A_PAN;2025-10-22_07-23-44_LIBRARY_EVP-AKE31ASW_EVP-AKE31A_PAN;;;;;Top;
TP_3.3V, TP_3V3, TP_BAT_GND, TP_GND, TP_ON, TP_OP, TP_RESET, TP_SCL, TP_SDA, TP_SWDCLK, TP_SWDIO, TP_SWO, TP_VBAT, TP_VREG;14;Test pad;HECTOR_WATCH_1_TP20R;HECTOR_WATCH_1_TPTP20R;;;;;Top;
U1;1;nRF52840;NORDIC_NRF_4_AQFN50P700X700X85_HS-74N;NRF52840_QF;;;;;Top;
U3;1;Check availability;SON50P200X200X80-9N;MAX17048G+T10;;;;;Top;
X1;1;;NORDIC_NRF_BT-XTAL_2016_N;32MHz;;;;;Top;
X2;1;;NORDIC_NRF_1_XTAL_3215_N;32.768kHz;;;;;Top;

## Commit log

2026-04-10 Add README.md with project documentation
    Added detailed project documentation for SmartWatch InkTime, including block diagram, bill of materials, hardware functionality, pin mapping, PCB design details, and repository structure.
2026-04-10 Add 3D render images to README
    Added 3D render images for top, bottom, and inner layers.
2026-04-10 Revise PCB design section in README
    Updated PCB design details and added specifications.
2026-04-10 Insert block diagram and update system overview
    Add block diagram image and update description.
2026-04-10 Update table header in README for clarity
2026-04-10 Update PCB section in README with new layout
2026-04-10 Add schematic section to README
    Added schematic section with images to README.
2026-04-10 Update PCB and Schematic section headings in README
2026-04-10 Fix schematic image references in README
2026-04-10 Include Apache License 2.0
    Added the Apache License 2.0 to the project.
2026-04-10 Update README to remove specific component listings
    Removed component details from the hardware section.
2026-04-10 Add new components to the README table
2026-04-10 Revise component details in README.md
    Updated component table with new part references and descriptions.
2026-04-20 Revise README with BOM and hardware details
    Updated the README.md to include a detailed Bill of Materials (BOM) section and improved the hardware description, including architecture and specifications.
2026-04-20 Update PCB design and schematic sections in README
2026-04-20 Fix formatting and image widths in README.md
    Corrected formatting issues in the PCB design section and adjusted image widths for better display.
2026-04-20 fisierul step cu exploaded view

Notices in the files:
parts and their libraries:
COPYRIGHT: Copyright (C) 2025 Ultra Librarian. All rights reserved.
COPYRIGHT: Copyright (C) 2024 Ultra Librarian. All rights reserved.
